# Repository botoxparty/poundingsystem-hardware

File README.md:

# Pounding System Hardware

This is the central repository for the Pounding System hardware design files.

## Modules

### Human Interface

### Audio board (TODO)

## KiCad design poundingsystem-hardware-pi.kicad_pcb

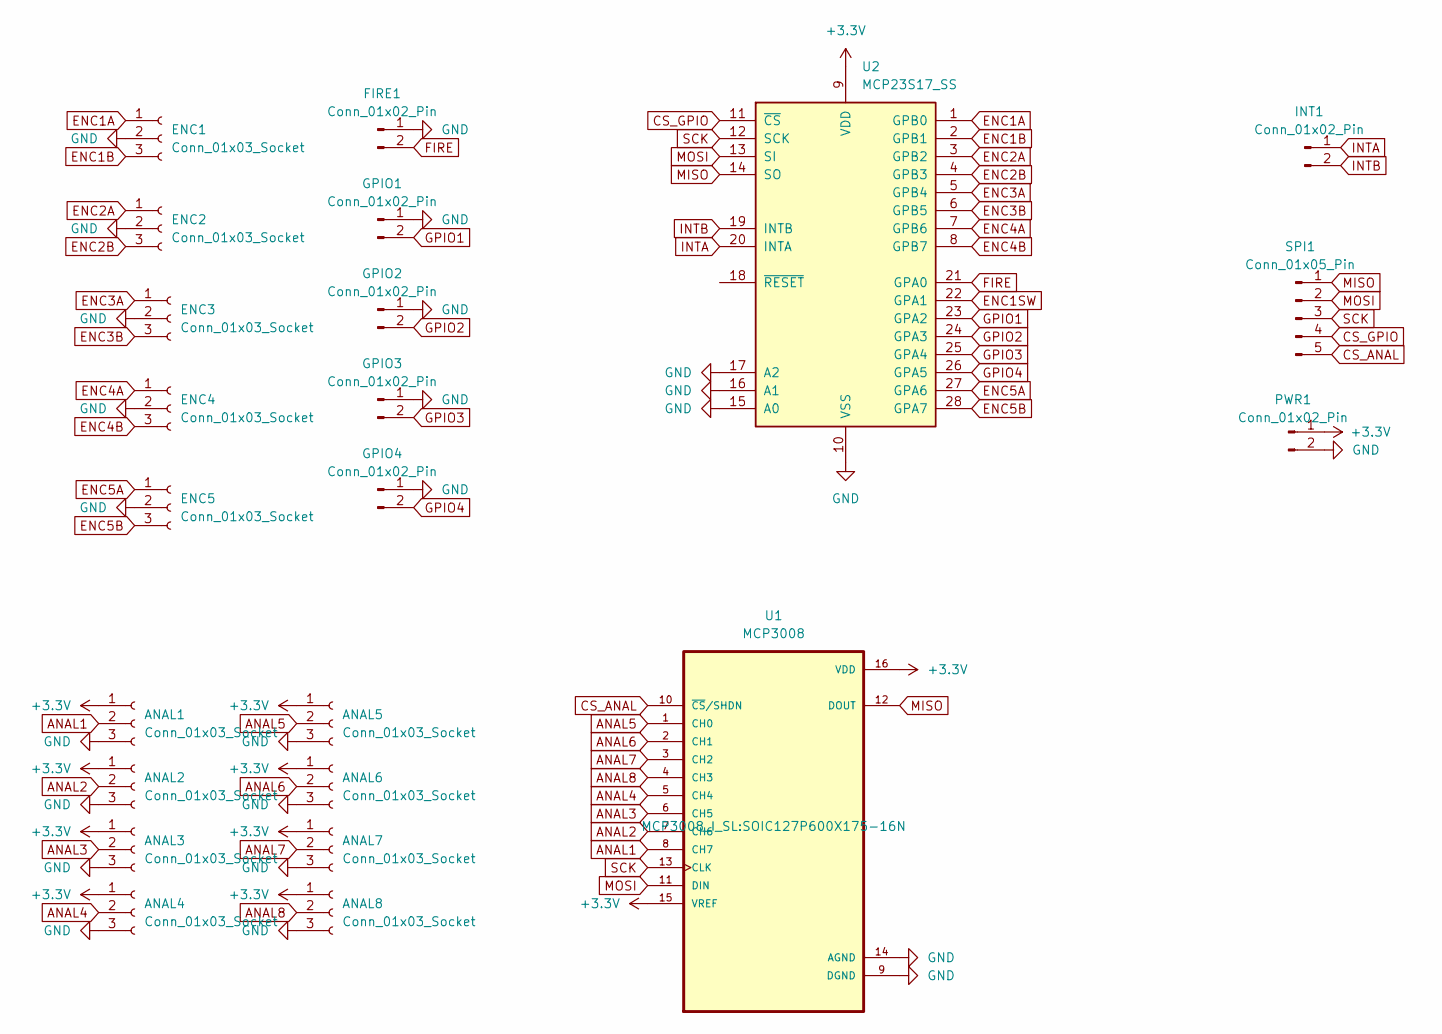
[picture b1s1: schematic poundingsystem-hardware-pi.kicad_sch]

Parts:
ANAL1, ANAL2, ANAL3, ANAL4, ANAL5, ANAL6, ANAL7, ANAL8: Conn_01x03_Socket; JST_XH_B3B-XH-AM_1x03_P2.50mm_Vertical
ENC1, ENC2, ENC3, ENC4, ENC5: Conn_01x03_Socket; JST_XH_B3B-XH-AM_1x03_P2.50mm_Vertical
FIRE1: Conn_01x02_Pin; JST_XH_B2B-XH-AM_1x02_P2.50mm_Vertical
GPIO1, GPIO2, GPIO3, GPIO4: Conn_01x02_Pin; JST_XH_B2B-XH-AM_1x02_P2.50mm_Vertical
INT1: Conn_01x02_Pin; JST_XH_B2B-XH-AM_1x02_P2.50mm_Vertical
PWR1: Conn_01x02_Pin; JST_XH_B2B-XH-AM_1x02_P2.50mm_Vertical
SPI1: Conn_01x05_Pin; JST_XH_B5B-XH-AM_1x05_P2.50mm_Vertical
U1: MCP3008; SOIC127P600X175-16N
U2: MCP23S17_SS; SSOP-28_5.3x10.2mm_P0.65mm

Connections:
+3.3V: ANAL1.1, ANAL2.1, ANAL3.1, ANAL4.1, ANAL5.1, ANAL6.1, ANAL7.1, ANAL8.1, PWR1.1, U1.15 (VREF), U1.16 (VDD), U2.9 (VDD)
ANAL1: ANAL1.2, U1.8 (CH7)
ANAL2: ANAL2.2, U1.7 (CH6)
ANAL3: ANAL3.2, U1.6 (CH5)
ANAL4: ANAL4.2, U1.5 (CH4)
ANAL5: ANAL5.2, U1.1 (CH0)
ANAL6: ANAL6.2, U1.2 (CH1)
ANAL7: ANAL7.2, U1.3 (CH2)
ANAL8: ANAL8.2, U1.4 (CH3)
CS_ANAL: SPI1.5, U1.10 (~CS/SHDN)
CS_GPIO: SPI1.4, U2.11 (~CS)
ENC1A: ENC1.1, U2.1 (GPB0)
ENC1B: ENC1.3, U2.2 (GPB1)
ENC1SW: U2.22 (GPA1)
ENC2A: ENC2.1, U2.3 (GPB2)
ENC2B: ENC2.3, U2.4 (GPB3)
ENC3A: ENC3.1, U2.5 (GPB4)
ENC3B: ENC3.3, U2.6 (GPB5)
ENC4A: ENC4.1, U2.7 (GPB6)
ENC4B: ENC4.3, U2.8 (GPB7)
ENC5A: ENC5.1, U2.27 (GPA6)
ENC5B: ENC5.3, U2.28 (GPA7)
FIRE: FIRE1.2, U2.21 (GPA0)
GND: ANAL1.3, ANAL2.3, ANAL3.3, ANAL4.3, ANAL5.3, ANAL6.3, ANAL7.3, ANAL8.3, ENC1.2, ENC2.2, ENC3.2, ENC4.2, ENC5.2, FIRE1.1, GPIO1.1, GPIO2.1, GPIO3.1, GPIO4.1, PWR1.2, U1.9 (DGND), U1.14 (AGND), U2.10 (VSS), U2.15 (A0), U2.16 (A1), U2.17 (A2)
GPIO1: GPIO1.2, U2.23 (GPA2)
GPIO2: GPIO2.2, U2.24 (GPA3)
GPIO3: GPIO3.2, U2.25 (GPA4)
GPIO4: GPIO4.2, U2.26 (GPA5)
INTA: INT1.1, U2.20 (INTA)
INTB: INT1.2, U2.19 (INTB)
MISO: SPI1.1, U1.12 (DOUT), U2.14 (SO)
MOSI: SPI1.2, U1.11 (DIN), U2.13 (SI)
SCK: SPI1.3, U1.13 (CLK), U2.12 (SCK)

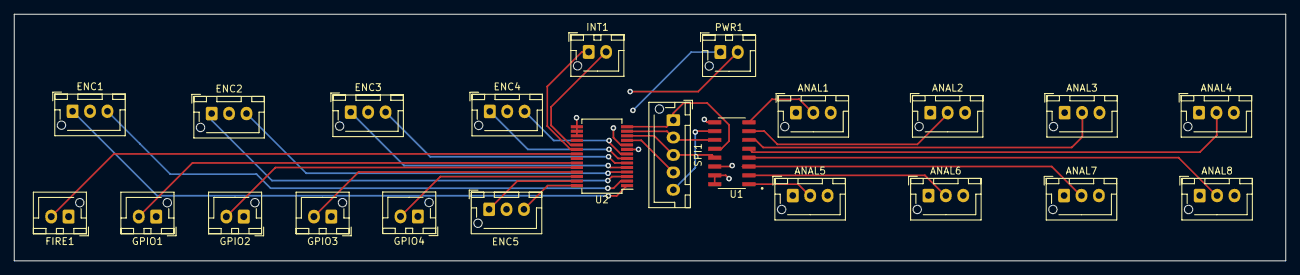
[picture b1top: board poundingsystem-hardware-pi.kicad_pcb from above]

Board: 4 copper layers, 182.5 x 35.4 mm, 23 parts (0 on the bottom side), 32 nets.

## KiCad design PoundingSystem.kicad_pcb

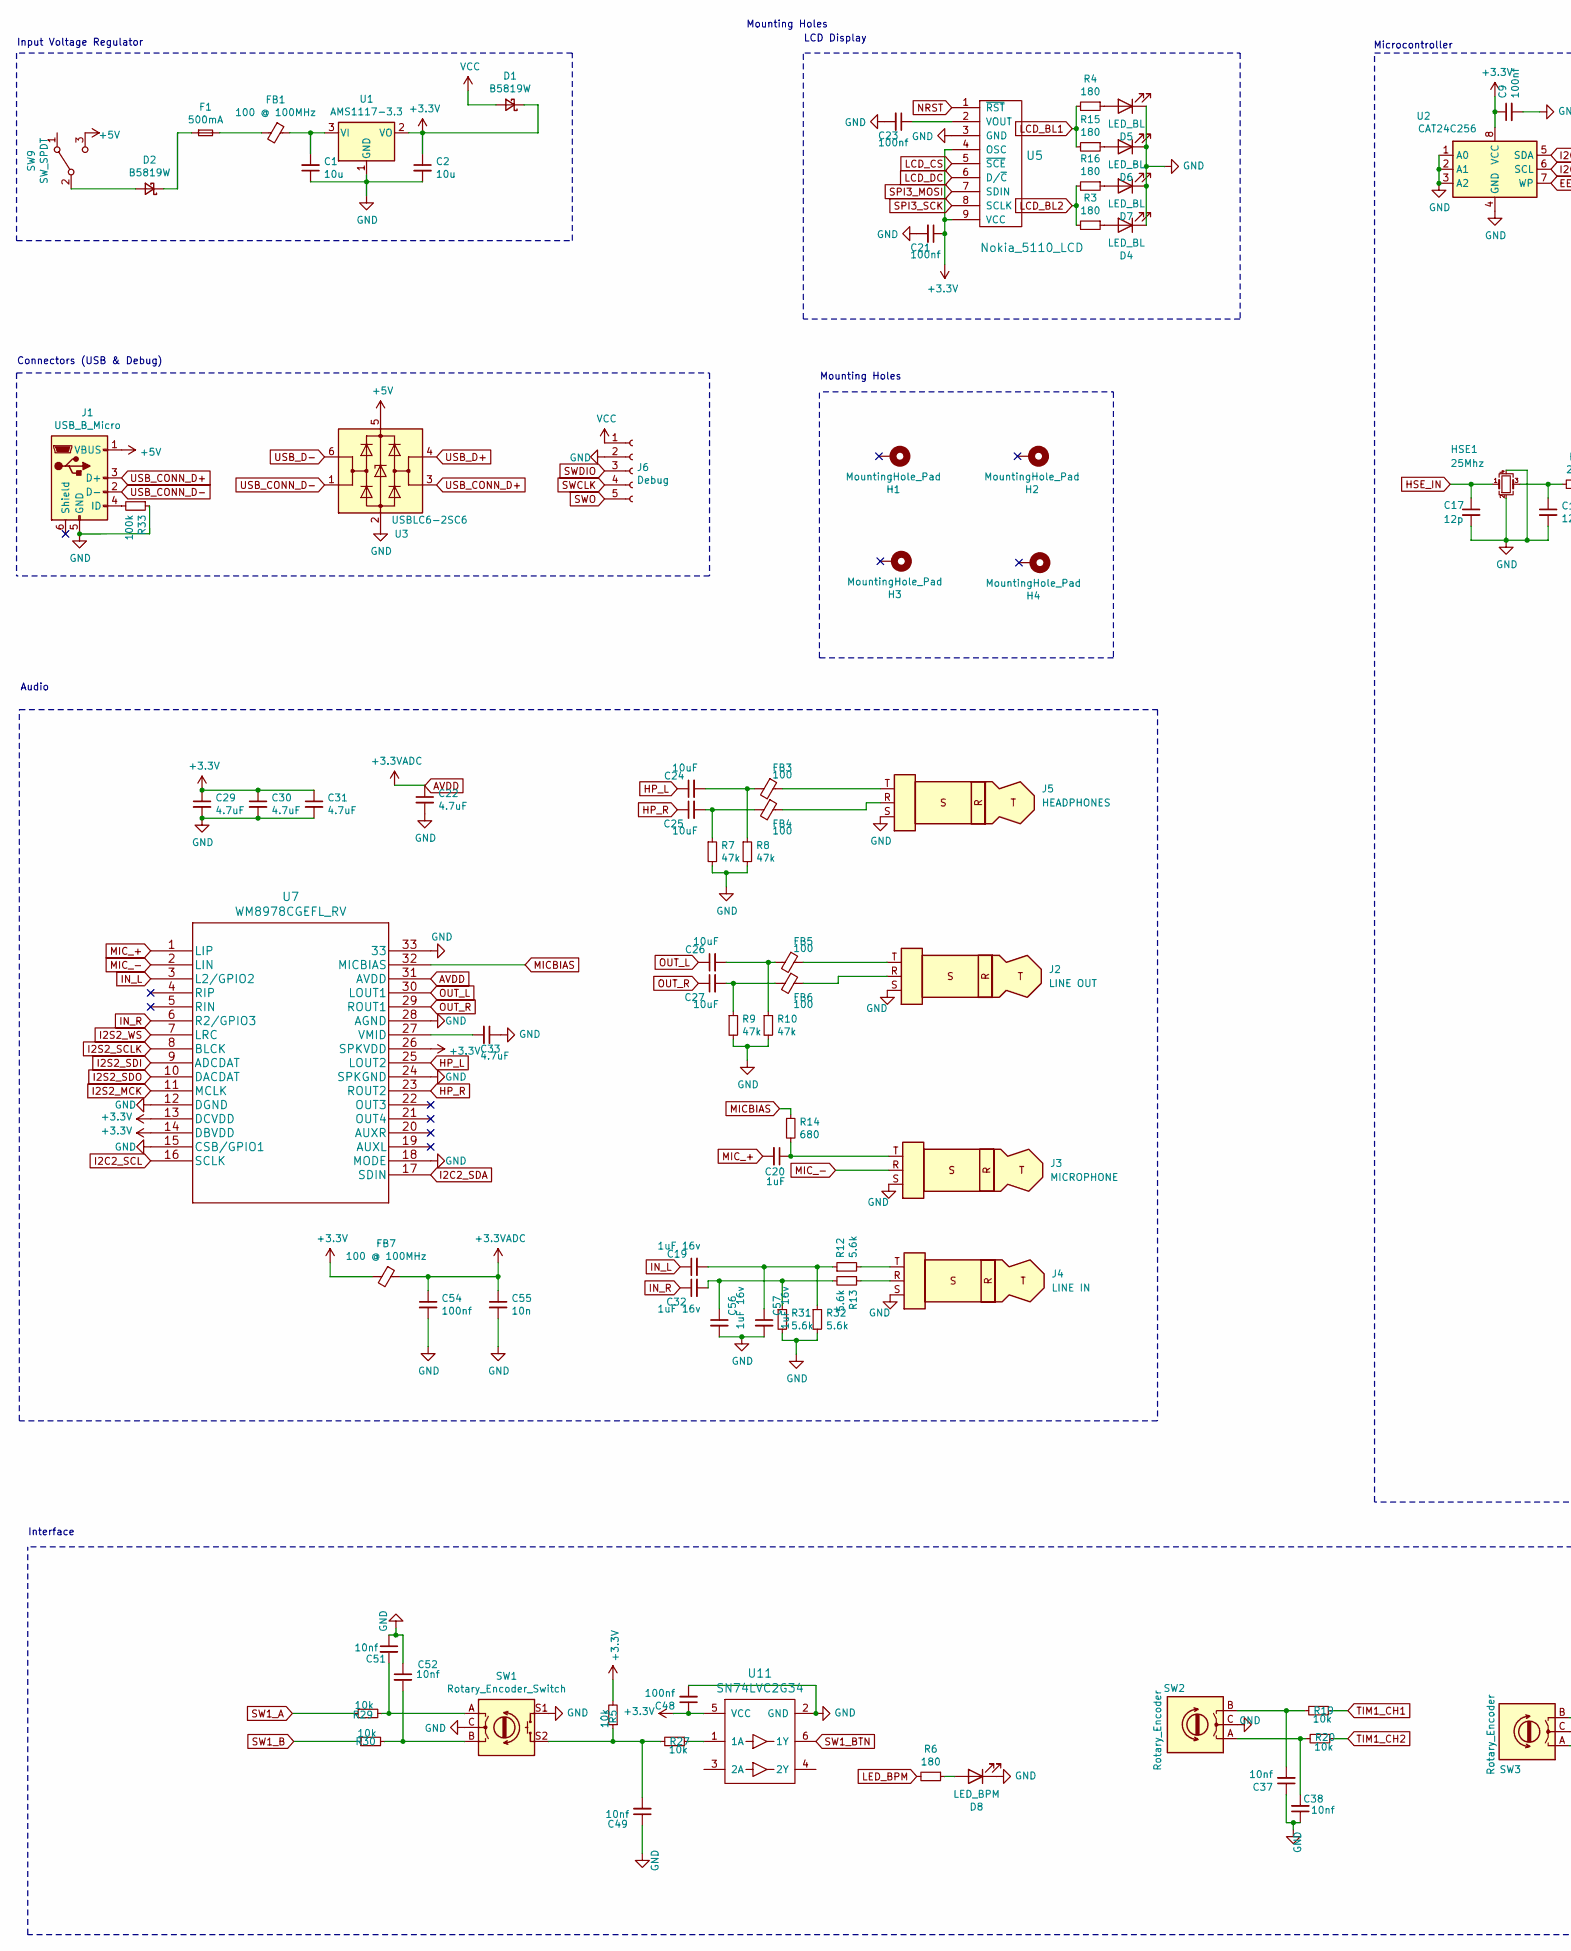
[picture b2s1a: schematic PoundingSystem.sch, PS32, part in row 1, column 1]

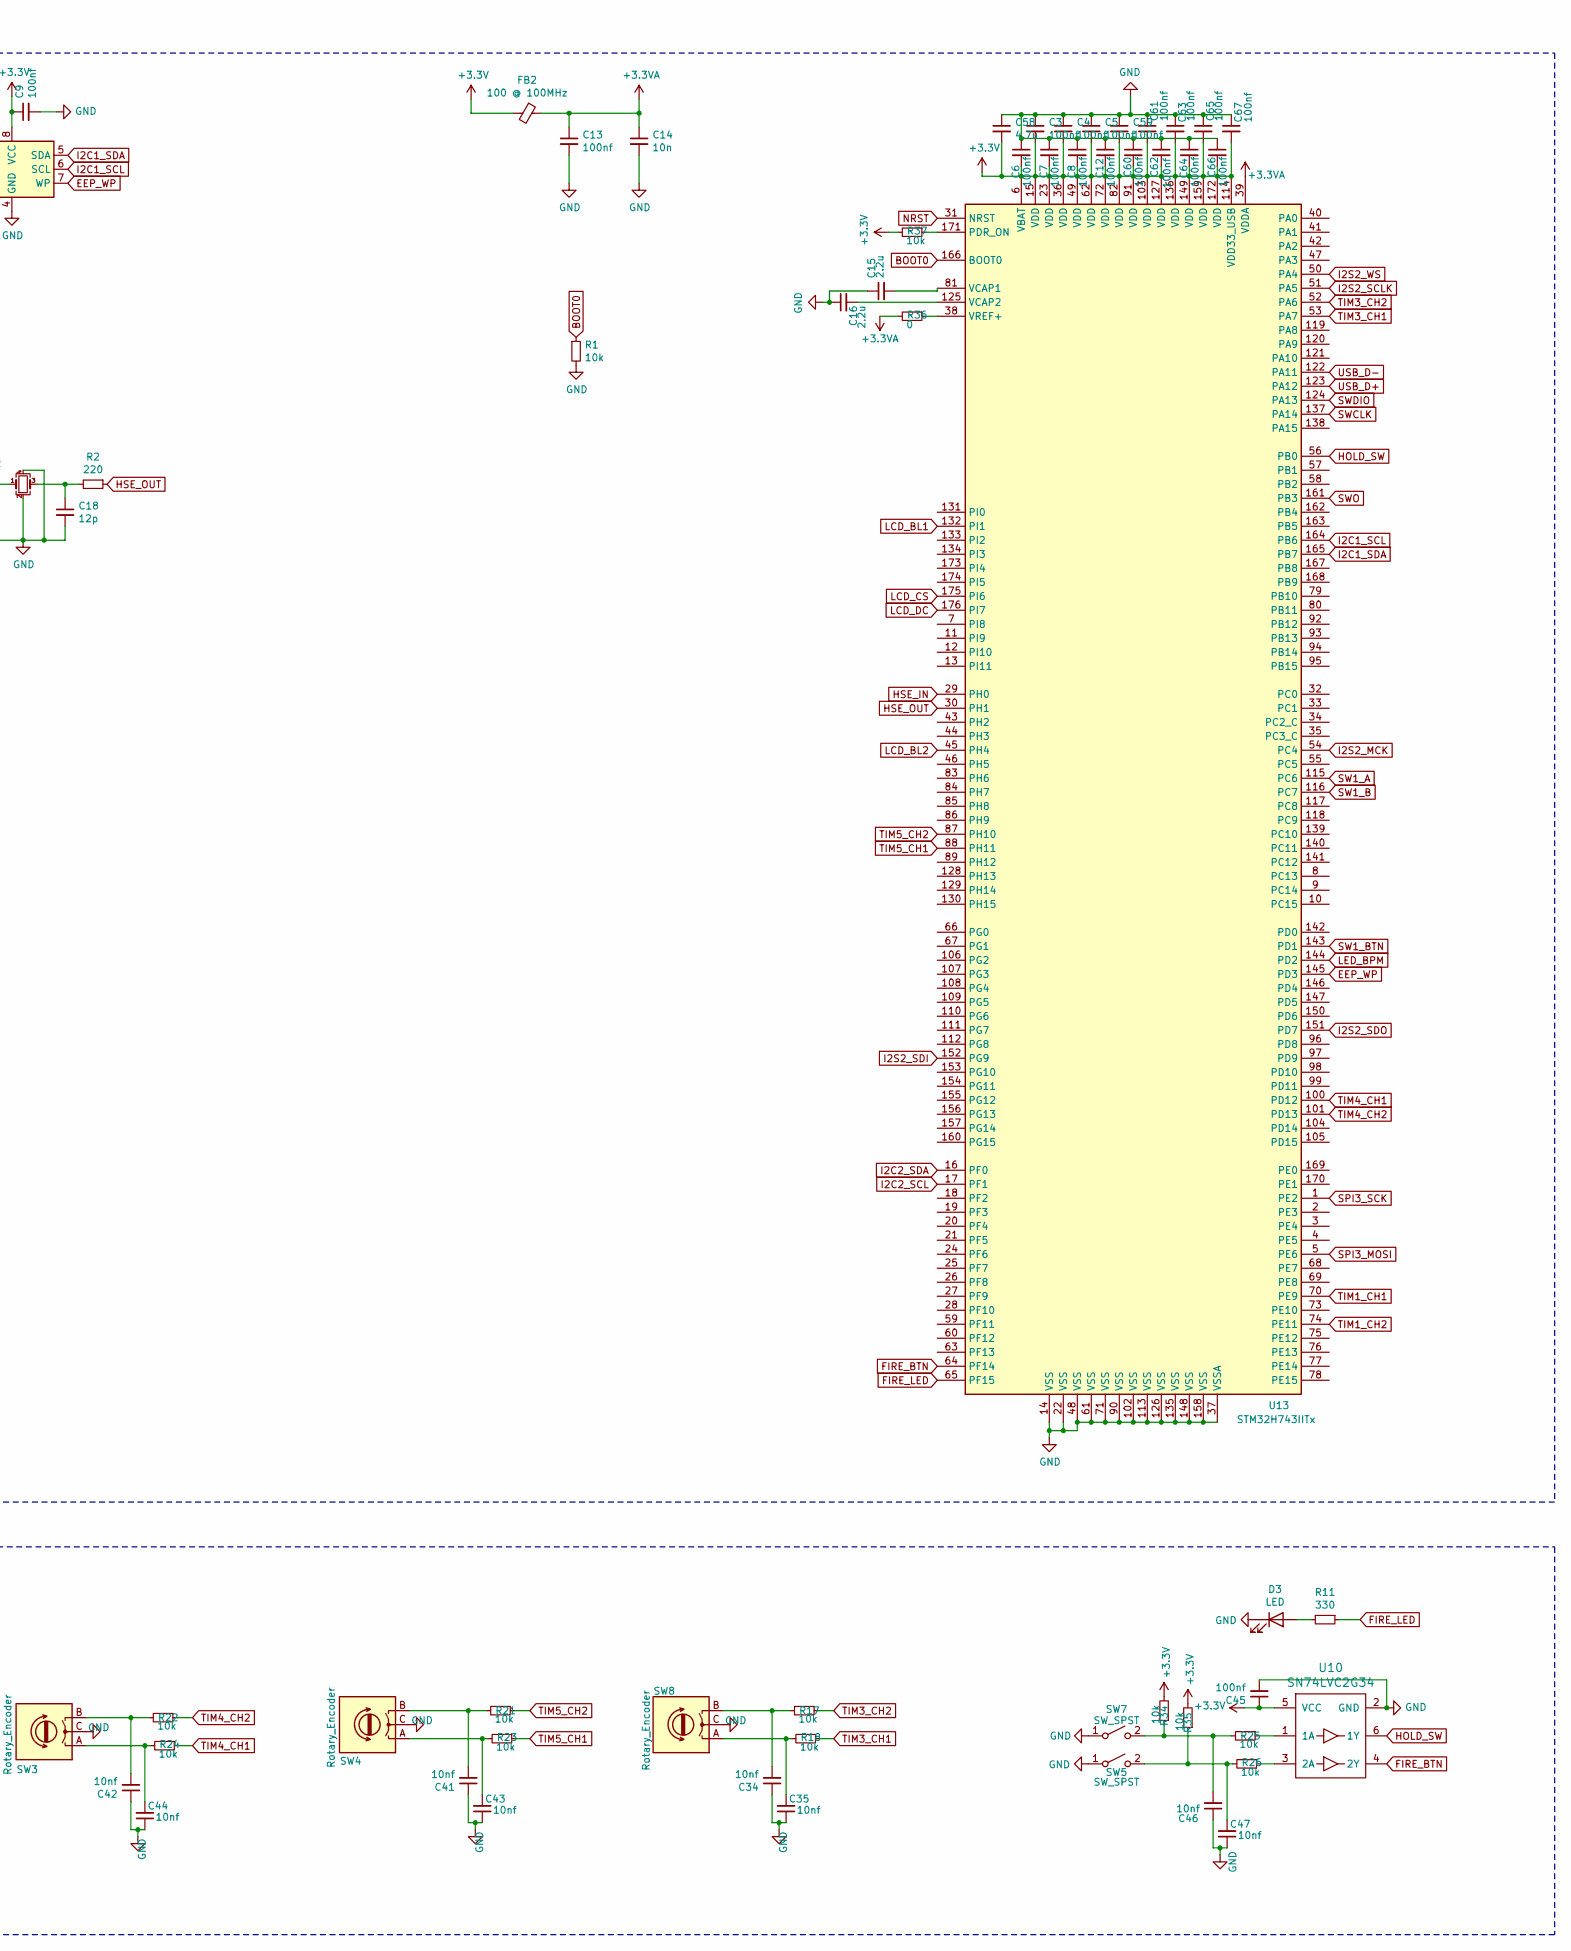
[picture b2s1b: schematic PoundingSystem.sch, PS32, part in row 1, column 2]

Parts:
C1, C2: 10u; C_0805_2012Metric; LCSC Part # C15850
C3, C4, C5, C6, C7, C8, C9, C12, C13, C21, C23, C45, C48, C54, C59, C60, C61, C62, C63, C64, C65, C66, C67: 100nf; C_0402_1005Metric; LCSC Part # C1525
C14, C55: 10n; C_0402_1005Metric; LCSC Part # C15195
C15, C16: 2.2u; C_0603_1608Metric; LCSC Part # C23630
C17, C18: 12p; C_0402_1005Metric; LCSC Part # C1547
C19, C32, C56, C57: 1uF 16v; C_0402_1005Metric; LCSC Part # C52923
C20: 1uF; C_0402_1005Metric; LCSC Part # C52923
C22, C29, C30, C31, C33: 4.7uF; C_0402_1005Metric; LCSC Part # C23733
C24, C25, C26, C27: 10uF; C_0402_1005Metric; LCSC Part # C15525
C34, C35, C37, C38, C41, C42, C43, C44, C46, C47, C49, C51, C52: 10nf; C_0402_1005Metric; LCSC Part # C15195
C58: 4.7u; C_0603_1608Metric; LCSC Part # C19702
D1, D2: B5819W; D_SOD-123; LCSC Part # C8598
D3: LED; LED_0603_1608Metric; LCSC Part # C2286
D4, D5, D6, D7: LED_BL; LED_0805_2012Metric; LCSC Part # C34499
D8: LED_BPM; LED_0805_2012Metric; LCSC Part # C192670
F1: 500mA; Fuse_0603_1608Metric; LCSC Part # C187605
FB1, FB2, FB7: 100 @ 100MHz; L_0805_2012Metric; LCSC Part # C1017
FB3, FB4, FB5, FB6: 100; L_0805_2012Metric; LCSC Part # C1017
H1, H2, H3, H4: MountingHole_Pad; MountingHole_2.2mm_M2_Pad_Via
HSE1: 25Mhz; Crystal_SMD_3225-4Pin_3.2x2.5mm; LCSC Part # C9006
J1: USB_B_Micro; USB_Micro-B_Molex-105017-0001; LCSC Part # C136000
J2: LINE OUT; AudioPJ-320B
J3: MICROPHONE; AudioPJ-320B
J4: LINE IN; AudioPJ-320B
J5: HEADPHONES; AudioPJ-320B
J6: Debug; PinHeader_1x05_P2.54mm_Vertical; LCSC Part # C390682
R1, R5, R17, R18, R19, R20, R21, R22, R23, R24, R25, R26, R27, R29, R30, R34, R35, R37: 10k; R_0402_1005Metric; LCSC Part # C25744
R2: 220; R_0402_1005Metric; LCSC Part # C25091
R3, R4, R6, R15, R16: 180; R_0603_1608Metric; LCSC Part # C22828
R7, R8, R9, R10: 47k; R_0805_2012Metric; LCSC Part # C17713
R11: 330; R_0402_1005Metric; LCSC Part # C25104
R12, R13, R31, R32: 5.6k; R_0805_2012Metric; LCSC Part # C4382
R14: 680; R_0805_2012Metric; LCSC Part # C17798
R33: 100k; R_0402_1005Metric; LCSC Part # C25741
R36: 0; R_0402_1005Metric; LCSC Part # C17168
SW1: Rotary_Encoder_Switch; RotaryEncoder_Alps_EC11E-Switch_Vertical_H20mm
SW2, SW3, SW4: Rotary_Encoder; RotaryEncoder_Alps_EC12E_Vertical_H20mm
SW5: SW_SPST; Cherry-MX-Low-Profile
SW7: SW_SPST; SW_PUSH_6mm_H4.3mm; LCSC Part # C141875
SW8: Rotary_Encoder; RotaryEncoder_Alps_EC12E_Vertical_H20mm_CircularMountingHol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
SW9: SW_SPDT; SS-1290; LCSC Part # C695418
U1: AMS1117-3.3; SOT-223-3_TabPin2; LCSC Part # C6186
U2: CAT24C256; SOIC-8-1EP_3.9x4.9mm_P1.27mm_EP2.29x3mm; LCSC Part # C6482
U3: USBLC6-2SC6; SOT-23-6; LCSC Part # C7519
U5: Nokia_5110_LCD; Nokia_5110-3310_LCD
U7: WM8978CGEFL_RV; WM8960CGEFL&slash_RV; LCSC Part # C323850
U10, U11: SN74LVC2G34; SOT-363_SC-70-6; LCSC Part # C14461
U13: STM32H743IITx; LQFP-176_24x24mm_P0.5mm; LCSC Part # C89597

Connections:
+3.3VA: C13.1, C14.1, FB2.1, R36.2, U13.39 (VDDA)
+3V3: C2.1, C3.2, C4.2, C5.2, C6.2, C7.2, C8.2, C9.1, C12.2, C21.1, C29.1, C30.1, C31.1, C45.1, C48.1, C58.2, C59.2, C60.2, C61.2, C62.2, C63.2, C64.2, C65.2, C66.2, C67.2, D1.1 (K), FB2.2, FB7.2, R5.2, R34.2, R35.2, R37.2, U1.2 (VO), U2.8 (VCC), U5.4 (OSC), U5.9 (VCC), U7.13 (DCVDD), U7.14 (DBVDD), U7.26 (SPKVDD), U10.5 (VCC), U11.5 (VCC), U13.6 (VBAT), U13.15 (VDD), U13.23 (VDD), U13.36 (VDD), U13.49 (VDD), U13.62 (VDD), U13.72 (VDD), U13.82 (VDD), U13.91 (VDD), U13.103 (VDD), U13.114 (VDD33_USB), U13.127 (VDD), U13.136 (VDD), U13.149 (VDD), U13.159 (VDD), U13.172 (VDD)
+5V: J1.1 (VBUS), SW9.3 (C), U3.5 (VBUS)
AVDD: C22.1, C54.1, C55.1, FB7.1, U7.31 (AVDD)
BOOT0: R1.1, U13.166 (BOOT0)
EEP_WP: U2.7 (WP), U13.145 (PD3)
FIRE_BTN: U10.4 (2Y), U13.64 (PF14)
FIRE_LED: R11.1, U13.65 (PF15)
GND: C1.1, C2.2, C3.1, C4.1, C5.1, C6.1, C7.1, C8.1, C9.2, C12.1, C13.2, C14.2, C15.1, C16.1, C17.2, C18.2, C21.2, C22.2, C23.2, C29.2, C30.2, C31.2, C33.1, C34.1, C35.1, C37.1, C38.1, C41.1, C42.1, C43.1, C44.1, C45.2, C46.1, C47.1, C48.2, C49.1, C51.1, C52.1, C54.2, C55.2, C56.2, C57.2, C58.1, C59.1, C60.1, C61.1, C62.1, C63.1, C64.1, C65.1, C66.1, C67.1, D3.1 (K), D4.1 (K), D5.1 (K), D6.1 (K), D7.1 (K), D8.1 (K), HSE1.2, HSE1.4, J1.5 (GND), J2.S, J3.S, J4.S, J5.S, J6.2, R1.2, R7.2, R8.2, R9.2, R10.2, R31.2, R32.2, R33.1, SW1.C, SW1.S1, SW2.C, SW3.C, SW4.C, SW5.1 (A), SW7.1 (A), SW8.C, U1.1 (GND), U2.1 (A0), U2.2 (A1), U2.3 (A2), U2.4 (GND), U3.2 (GND), U5.3 (GND), U7.12 (DGND), U7.15 (CSB/GPIO1), U7.18 (MODE), U7.24 (SPKGND), U7.28 (AGND), U7.33, U10.2 (GND), U11.2 (GND), U13.14 (VSS), U13.22 (VSS), U13.37 (VSSA), U13.48 (VSS), U13.61 (VSS), U13.71 (VSS), U13.90 (VSS), U13.102 (VSS), U13.113 (VSS), U13.126 (VSS), U13.135 (VSS), U13.148 (VSS), U13.158 (VSS)
HOLD_SW: U10.6 (1Y), U13.56 (PB0)
HP_L: C24.1, U7.25 (LOUT2)
HP_R: C25.1, U7.23 (ROUT2)
HSE_IN: C17.1, HSE1.1, U13.29 (PH0)
HSE_OUT: R2.1, U13.30 (PH1)
I2C1_SCL: U2.6 (SCL), U13.164 (PB6)
I2C1_SDA: U2.5 (SDA), U13.165 (PB7)
I2C2_SCL: U7.16 (SCLK), U13.17 (PF1)
I2C2_SDA: U7.17 (SDIN), U13.16 (PF0)
I2S2_MCK: U7.11 (MCLK), U13.54 (PC4)
I2S2_SCLK: U7.8 (BLCK), U13.51 (PA5)
I2S2_SDI: U7.9 (ADCDAT), U13.152 (PG9)
I2S2_SDO: U7.10 (DACDAT), U13.151 (PD7)
I2S2_WS: U7.7 (LRC), U13.50 (PA4)
IN_L: C19.1, U7.3 (L2/GPIO2)
IN_R: C32.1, U7.6 (R2/GPIO3)
LCD_BL1: R4.2, R15.2, U13.132 (PI1)
LCD_BL2: R3.2, R16.2, U13.45 (PH4)
LCD_CS: U5.5 (~SCE), U13.175 (PI6)
LCD_DC: U5.6 (D/~C), U13.176 (PI7)
LED_BPM: R6.2, U13.144 (PD2)
MICBIAS: R14.1, U7.32 (MICBIAS)
MIC_+: C20.2, U7.1 (LIP)
MIC_-: J3.R, U7.2 (LIN)
NRST: U5.1 (~RST), U13.31 (NRST)
unnamed: C1.2, FB1.1, U1.3 (VI)
unnamed: C15.2, U13.81 (VCAP1)
unnamed: C16.2, U13.125 (VCAP2)
unnamed: C18.1, HSE1.3, R2.2
unnamed: C19.2, C57.1, R12.1, R32.1
unnamed: C20.1, J3.T, R14.2
unnamed: C23.1, U5.2 (VOUT)
unnamed: C24.2, FB3.2, R8.1
unnamed: C25.2, FB4.2, R7.1
unnamed: C26.2, FB5.2, R10.1
unnamed: C27.2, FB6.2, R9.1
unnamed: C32.2, C56.1, R13.2, R31.1
unnamed: C33.2, U7.27 (VMID)
unnamed: C34.2, R17.2, SW8.B
unnamed: C35.2, R18.2, SW8.A
unnamed: C37.2, R19.2, SW2.B
unnamed: C38.2, R20.2, SW2.A
unnamed: C41.2, R21.2, SW4.B
unnamed: C42.2, R22.2, SW3.B
unnamed: C43.2, R23.2, SW4.A
unnamed: C44.2, R24.2, SW3.A
unnamed: C46.2, R25.2, R34.1, SW7.2 (B)
unnamed: C47.2, R26.2, R35.1, SW5.2 (B)
unnamed: C49.2, R5.1, R27.2, SW1.S2
unnamed: C51.2, R29.2, SW1.A
unnamed: C52.2, R30.2, SW1.B
unnamed: D2.1 (K), F1.1
unnamed: D2.2 (A), SW9.2 (B)
unnamed: D3.2 (A), R11.2
unnamed: D4.2 (A), R3.1
unnamed: D5.2 (A), R4.1
unnamed: D6.2 (A), R15.1
unnamed: D7.2 (A), R16.1
unnamed: D8.2 (A), R6.1
unnamed: F1.2, FB1.2
unnamed: FB3.1, J5.T
unnamed: FB4.1, J5.R
unnamed: FB5.1, J2.T
unnamed: FB6.1, J2.R
unnamed 74: H2.1; also elsewhere on the board
unnamed: J1.4 (ID), R33.2
unnamed: J4.R, R13.1
unnamed: J4.T, R12.2
unnamed: R25.1, U10.1 (1A)
unnamed: R26.1, U10.3 (2A)
unnamed: R27.1, U11.1 (1A)
unnamed: R36.1, U13.38 (VREF+)
unnamed: R37.1, U13.171 (PDR_ON)
OUT_L: C26.1, U7.30 (LOUT1)
OUT_R: C27.1, U7.29 (ROUT1)
SPI4_MOSI: U5.7 (SDIN), U13.5 (PE6)
SPI4_SCK: U5.8 (SCLK), U13.1 (PE2)
SW1_A: R29.1, U13.115 (PC6)
SW1_B: R30.1, U13.116 (PC7)
SW1_BTN: U11.6 (1Y), U13.143 (PD1)
SWCLK: J6.4, U13.137 (PA14)
SWDIO: J6.3, U13.124 (PA13)
SWO: J6.5, U13.161 (PB3)
TIM1_CH1: R19.1, U13.70 (PE9)
TIM1_CH2: R20.1, U13.74 (PE11)
TIM3_CH1: R18.1, U13.53 (PA7)
TIM3_CH2: R17.1, U13.52 (PA6)
TIM4_CH1: R24.1, U13.100 (PD12)
TIM4_CH2: R22.1, U13.101 (PD13)
TIM5_CH1: R23.1, U13.88 (PH11)
TIM5_CH2: R21.1, U13.87 (PH10)
USB_CONN_D+: J1.3 (D+), U3.3 (I/O2)
USB_CONN_D-: J1.2 (D-), U3.1 (I/O1)
USB_D+: U3.4 (I/O2), U13.123 (PA12)
USB_D-: U3.6 (I/O1), U13.122 (PA11)
VCC: D1.2 (A), J6.1

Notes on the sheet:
Input Voltage Regulator
Microcontroller
Connectors (USB & Debug)
Interface
Audio
Mounting Holes
LCD Display

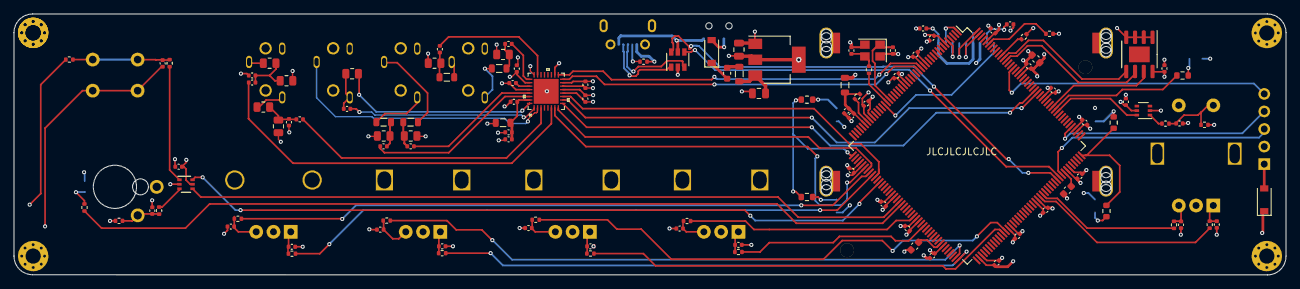
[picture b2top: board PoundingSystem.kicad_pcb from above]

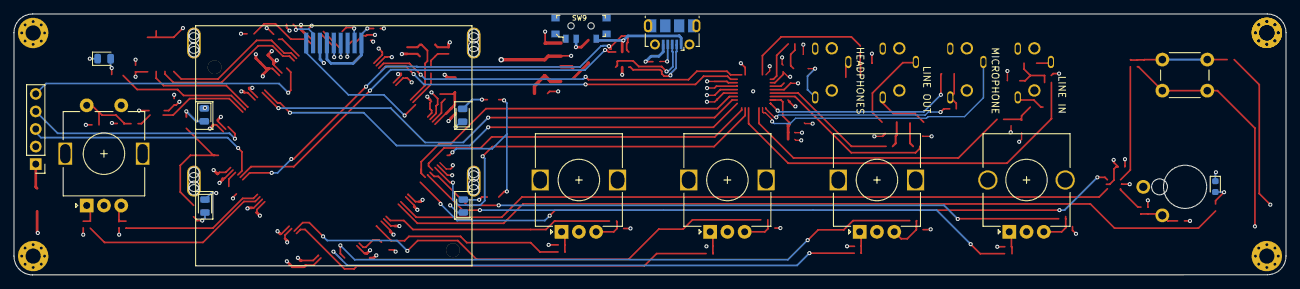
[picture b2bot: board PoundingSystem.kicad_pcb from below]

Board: 4 copper layers, 184.2 x 37.8 mm, 139 parts (21 on the bottom side), 105 nets.

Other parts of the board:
H2#2: MountingHole_Pad; MountingHole_2.2mm_M2_Pad_Via

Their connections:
unnamed 74: H2#2.1; also elsewhere on the board

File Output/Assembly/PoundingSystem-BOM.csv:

Comment,Designator,Footprint,LCSC
"10u","C1,C2","Capacitor_SMD:C_0805_2012Metric","C15850"
"100nf","C3,C4,C5,C6,C7,C8,C9,C12,C13,C21,C23,C45,C48,C54,C59,C60,C61,C62,C63,C64,C65,C66,C67","Capacitor_SMD:C_0402_1005Metric","C1525"
"10n","C14,C55","Capacitor_SMD:C_0402_1005Metric","C15195"
"2.2u","C15,C16","Capacitor_SMD:C_0603_1608Metric","C23630"
"12p","C17,C18","Capacitor_SMD:C_0402_1005Metric","C1547"
"1uF 16v","C19,C32,C56,C57","Capacitor_SMD:C_0402_1005Metric","C52923"
"1uF","C20","Capacitor_SMD:C_0402_1005Metric","C52923"
"10uF","C24,C25,C26,C27","Capacitor_SMD:C_0402_1005Metric","C15525"
"4.7uF","C22,C29,C30,C31,C33","Capacitor_SMD:C_0402_1005Metric","C23733"
"10nf","C34,C35,C37,C38,C41,C42,C43,C44,C46,C47,C49,C51,C52","Capacitor_SMD:C_0402_1005Metric","C15195"
"4.7u","C58","Capacitor_SMD:C_0603_1608Metric","C19702"
"B5819W","D1,D2","Diode_SMD:D_SOD-123","C8598"
"LED","D3","LED_SMD:LED_0603_1608Metric","C2286"
"LED_BL","D4,D5,D6,D7","LED_SMD:LED_0805_2012Metric","C34499"
"LED_BPM","D8","LED_SMD:LED_0805_2012Metric","C192670"
"500mA","F1","Fuse:Fuse_0603_1608Metric","C187605"
"100 @ 100MHz","FB1,FB2,FB7","Inductor_SMD:L_0805_2012Metric","C1017"
"100","FB3,FB4,FB5,FB6","Inductor_SMD:L_0805_2012Metric","C1017"
"MountingHole_Pad","H1,H2,H3,H4","MountingHole:MountingHole_2.2mm_M2_Pad_Via",""
"25Mhz","HSE1","Crystal:Crystal_SMD_3225-4Pin_3.2x2.5mm","C9006"
"USB_B_Micro","J1","Connector_USB:USB_Micro-B_Molex-105017-0001","C136000"
"LINE OUT","J2","AudioJack:AudioPJ-320B",""
"MICROPHONE","J3","AudioJack:AudioPJ-320B",""
"LINE IN","J4","AudioJack:AudioPJ-320B",""
"HEADPHONES","J5","AudioJack:AudioPJ-320B",""
"Debug","J6","Connector_PinHeader_2.54mm:PinHeader_1x05_P2.54mm_Vertical","C390682"
"10k","R1,R5,R17,R18,R19,R20,R21,R22,R23,R24,R25,R26,R27,R29,R30,R34,R35,R37","Resistor_SMD:R_0402_1005Metric","C25744"
"330","R11","Resistor_SMD:R_0402_1005Metric","C25104"
"680","R14","Resistor_SMD:R_0805_2012Metric","C17798"
"220","R2","Resistor_SMD:R_0402_1005Metric","C25091"
"180","R3,R4,R6,R15,R16","Resistor_SMD:R_0603_1608Metric","C22828"
"5.6k","R12,R13,R31,R32","Resistor_SMD:R_0805_2012Metric","C4382"
"100k","R33","Resistor_SMD:R_0402_1005Metric","C25741"
"0","R36","Resistor_SMD:R_0402_1005Metric","C17168"
"47k","R7,R8,R9,R10","Resistor_SMD:R_0805_2012Metric","C17713"
"Rotary_Encoder_Switch","SW1","Rotary_Encoder:RotaryEncoder_Alps_EC11E-Switch_Vertical_H20mm",""
"Rotary_Encoder","SW2,SW3,SW4","Rotary_Encoder:RotaryEncoder_Alps_EC12E_Vertical_H20mm",""
"SW_SPST","SW5","CherryMX:Cherry-MX-Low-Profile",""
"SW_SPST","SW7","Button_Switch_THT:SW_PUSH_6mm_H4.3mm","C141875"
"Rotary_Encoder","SW8","Rotary_Encoder:RotaryEncoder_Alps_EC12E_Vertical_H20mm_CircularMountingHoles",""
"SW_SPDT","SW9","ultimate_library:SS-1290","C695418"
"AMS1117-3.3","U1","Package_TO_SOT_SMD:SOT-223-3_TabPin2","C6186"
"SN74LVC2G34","U10,U11","Package_TO_SOT_SMD:SOT-23-6","C14461"
"STM32H743IITx","U13","Package_QFP:LQFP-176_24x24mm_P0.5mm","C89597"
"CAT24C256","U2","Package_SO:SOIC-8-1EP_3.9x4.9mm_P1.27mm_EP2.29x3mm","C6482"
"USBLC6-2SC6","U3","Package_TO_SOT_SMD:SOT-23-6","C7519"
"Nokia_5110_LCD","U5","NokiaLCD:Nokia_5110-3310_LCD",""
"WM8978CGEFL_RV","U7","WM8960:WM8960CGEFL&slash_RV","C323850"

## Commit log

2021-01-30 h7 version;
2021-02-06 switch MPU to stm32h7
2021-02-06 update render
2021-02-08 production: generate production files
2021-03-08 fix: update schematic labels
2024-02-21 Start module for interface
2024-02-21 Add README
2024-02-21 Add interface screenshots

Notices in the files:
parts and their libraries:
Copyright 2016 Accelerated Designs. All rights reserved.
